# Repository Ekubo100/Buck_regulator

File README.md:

# Buck_regulator

For the values of R3 and R2, i calculated them according to formulas given in the LM5017 datasheet.

I couldn't change the text ratio in board layout as it was locked at 8%.

The Forward/Back Annotation is not active because i tried to keep the type 3 minimum ripple configuration in schematic only.

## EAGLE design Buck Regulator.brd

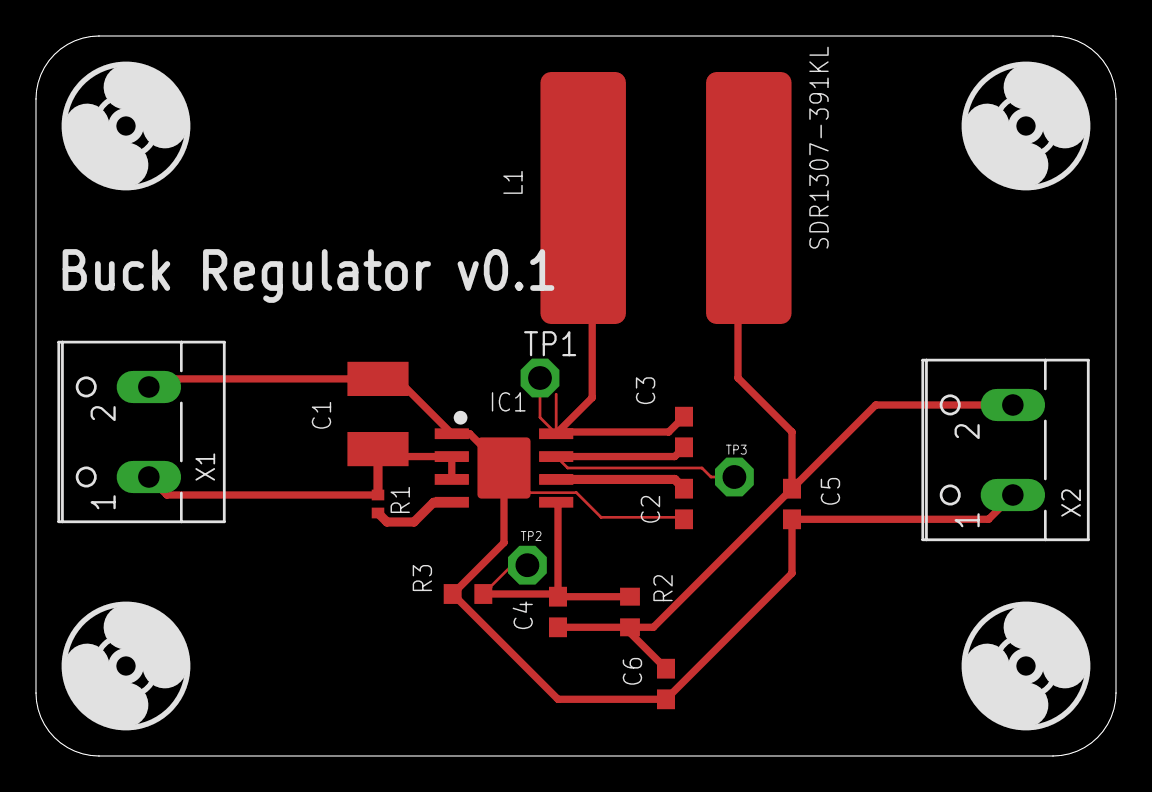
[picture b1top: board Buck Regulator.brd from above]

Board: 2 copper layers, 60.0 x 40.0 mm, 20 parts (0 on the bottom side), 8 nets.

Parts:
C1: 2.2uF/150V; C1812
C2: 1uF; C0603
C3: 10nF; C0603
C4: 4.7nF; C0603
C5, C6: 4.7uF; C0603
H1, H2, H3, H4: MOUNT-HOLE3.2; 3,2
IC1: LM5017; SO-08-EP
L1: SDR1307-391KL
R1: 499k; R0402
R2: 8.79kΩ; R0603
R3: 1kΩ; R0603
TP1, TP2, TP3: PTR1PAD1-13; P1-13
X1, X2: W237-102

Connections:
+12V: C4.1, C5.1, C6.1, L1.2, R2.2, X2.2
FB: C4.2, IC1.5, R2.1, R3.2, TP2.TP
GND: C1.2, C2.2, C5.2, C6.2, IC1.1, IC1.9, R3.1, X1.2, X2.1
unnamed: C2.1, IC1.6
unnamed: C3.1, IC1.7, TP3.TP
unnamed: C3.2, IC1.8, L1.1, TP1.TP
unnamed: IC1.4, R1.2
VIN_HV: C1.1, IC1.2, IC1.3, R1.1, X1.1

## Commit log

2021-10-14 Create gerber
